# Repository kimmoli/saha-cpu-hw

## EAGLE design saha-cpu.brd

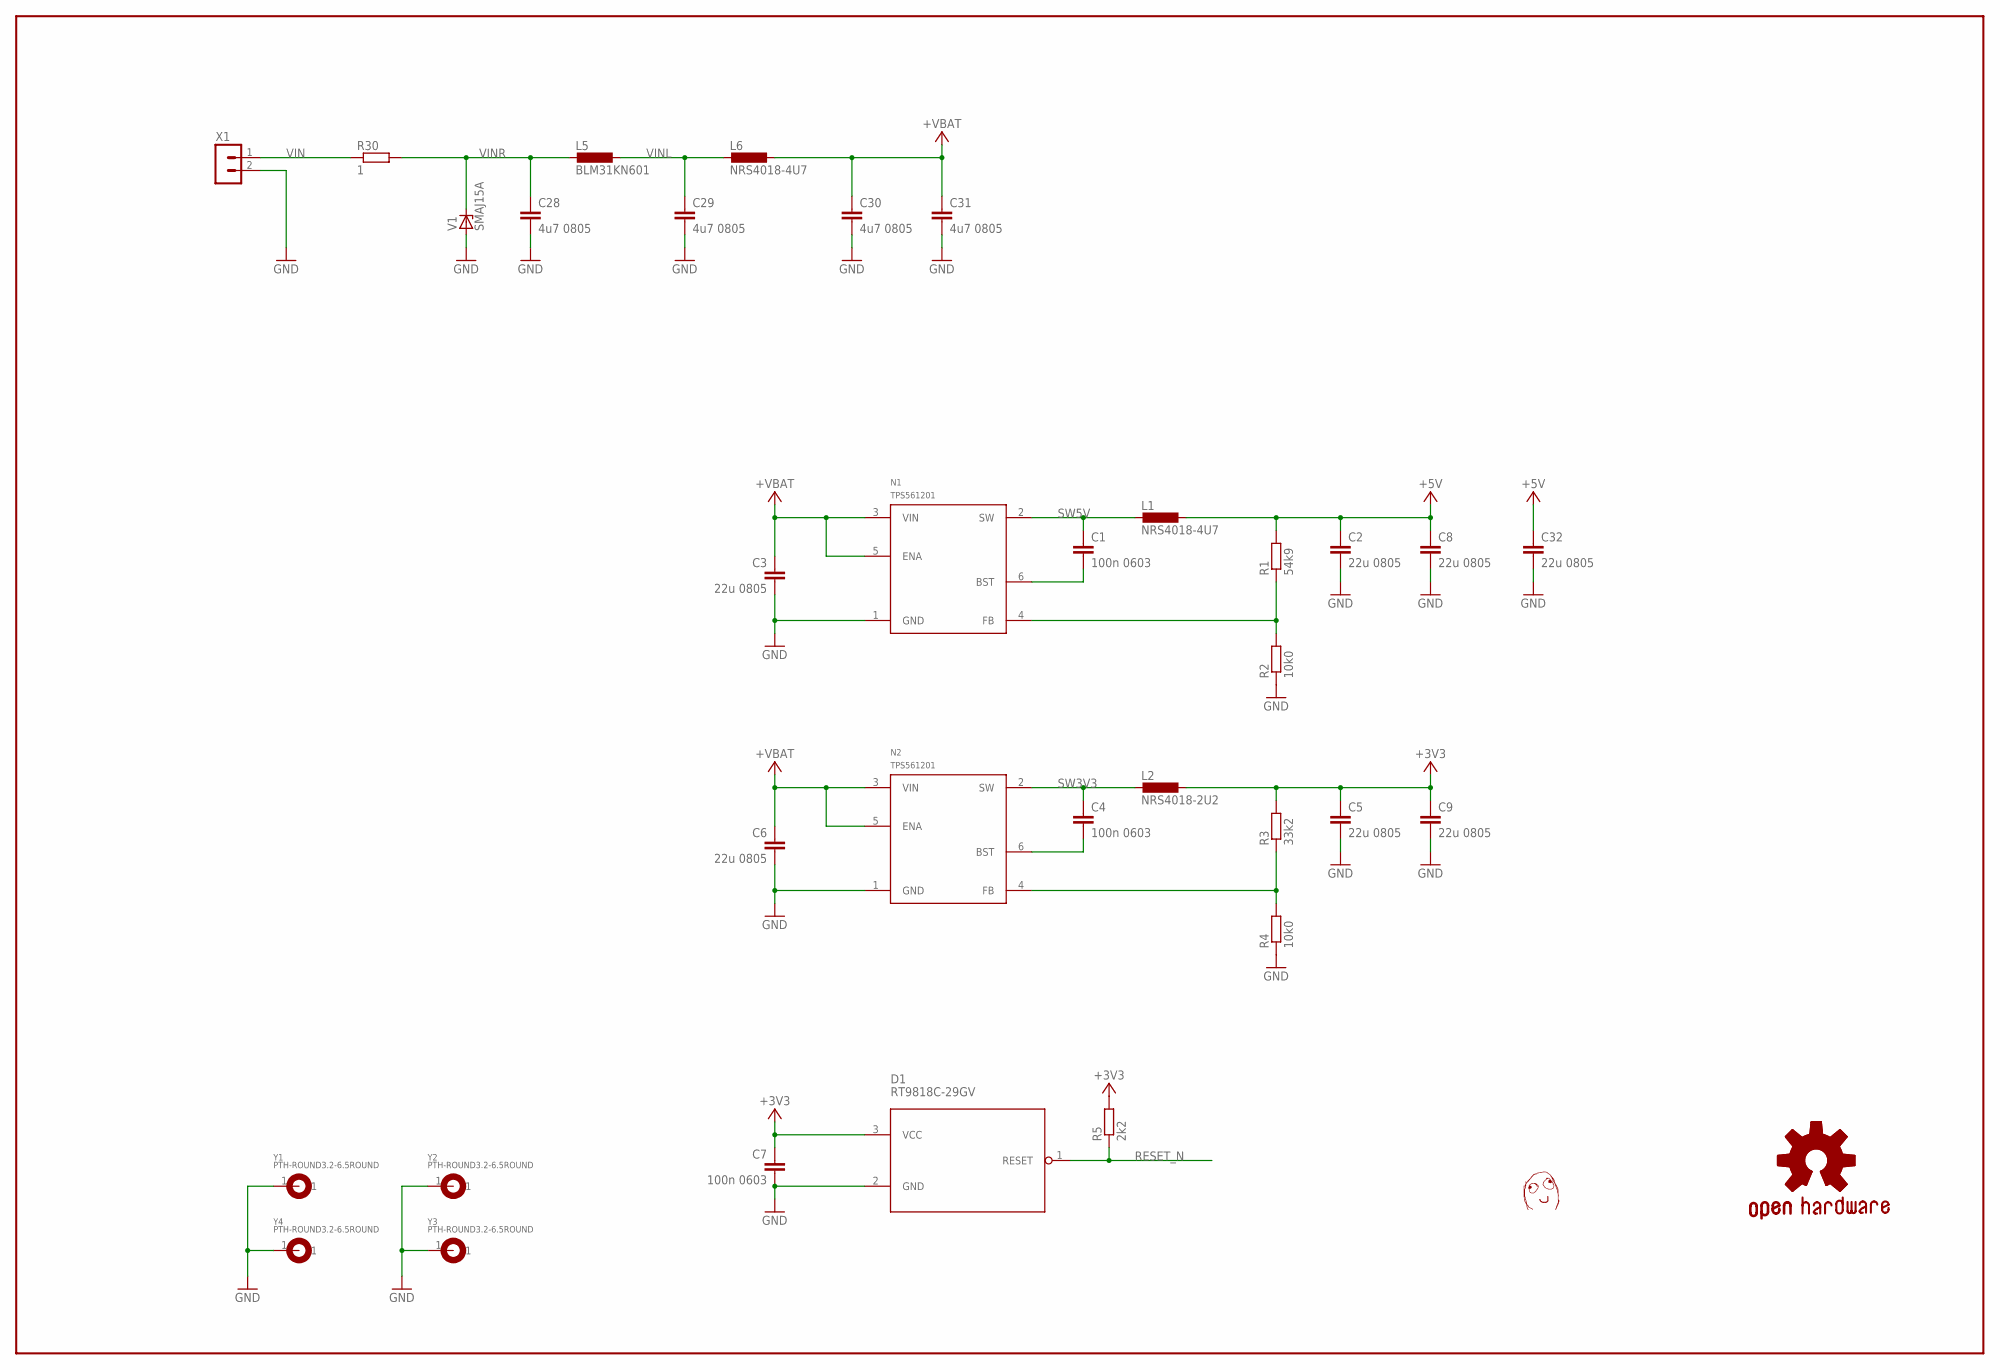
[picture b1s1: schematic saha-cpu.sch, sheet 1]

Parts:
C1, C4, C7: 100n 0603; C0603
C2, C3, C5, C6, C8, C9, C32: 22u 0805; C0805
C28, C29, C30, C31: 4u7 0805; C0805
D1: RT9818C-29GV; SOT23
L1, L6: NRS4018-4U7; NRS4018
L2: NRS4018-2U2; NRS4018
L5: BLM31KN601; R1206
N1, N2: TPS561201; OMAT_IC_2_SOT23-6
R1: 54k9; R0603
R2, R4: 10k0; R0603
R3: 33k2; R0603
R5: 2k2; R0603
R30: 1; R2512
U$1: DAFUG
V1: SMAJ15A; DO214AC
X1: TE_RUUVILIITIN2
Y1, Y2, Y3, Y4: PTH-ROUND3.2-6.5ROUND; EKE_PTH-3.2-6.5

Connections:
+3V3: C5.1, C7.1, C9.1, D1.3 (VCC), L2.1, R3.2, R5.2; also elsewhere on the board
+5V: C2.1, C8.1, C32.1, L1.1, R1.2; also elsewhere on the board
+VBAT: C3.1, C6.1, C30.1, C31.1, L6.1, N1.3 (VIN), N1.5 (ENA), N2.3 (VIN), N2.5 (ENA); also elsewhere on the board
GND: C2.2, C3.2, C5.2, C6.2, C7.2, C8.2, C9.2, C28.2, C29.2, C30.2, C31.2, C32.2, D1.2 (GND), N1.1 (GND), N2.1 (GND), R2.1, R4.1, V1.A, X1.2, Y1.1, Y2.1, Y3.1, Y4.1; also elsewhere on the board
unnamed: N2.4 (FB), R3.1, R4.2
unnamed: N1.4 (FB), R1.1, R2.2
unnamed: C1.2, N1.6 (BST)
unnamed: C4.2, N2.6 (BST)
RESET_N: D1.1 (RESET), R5.1; also elsewhere on the board
SW3V3: C4.1, L2.2, N2.2 (SW)
SW5V: C1.1, L1.2, N1.2 (SW)
VIN: R30.1, X1.1
VINL: C29.1, L5.1, L6.2
VINR: C28.1, L5.2, R30.2, V1.C

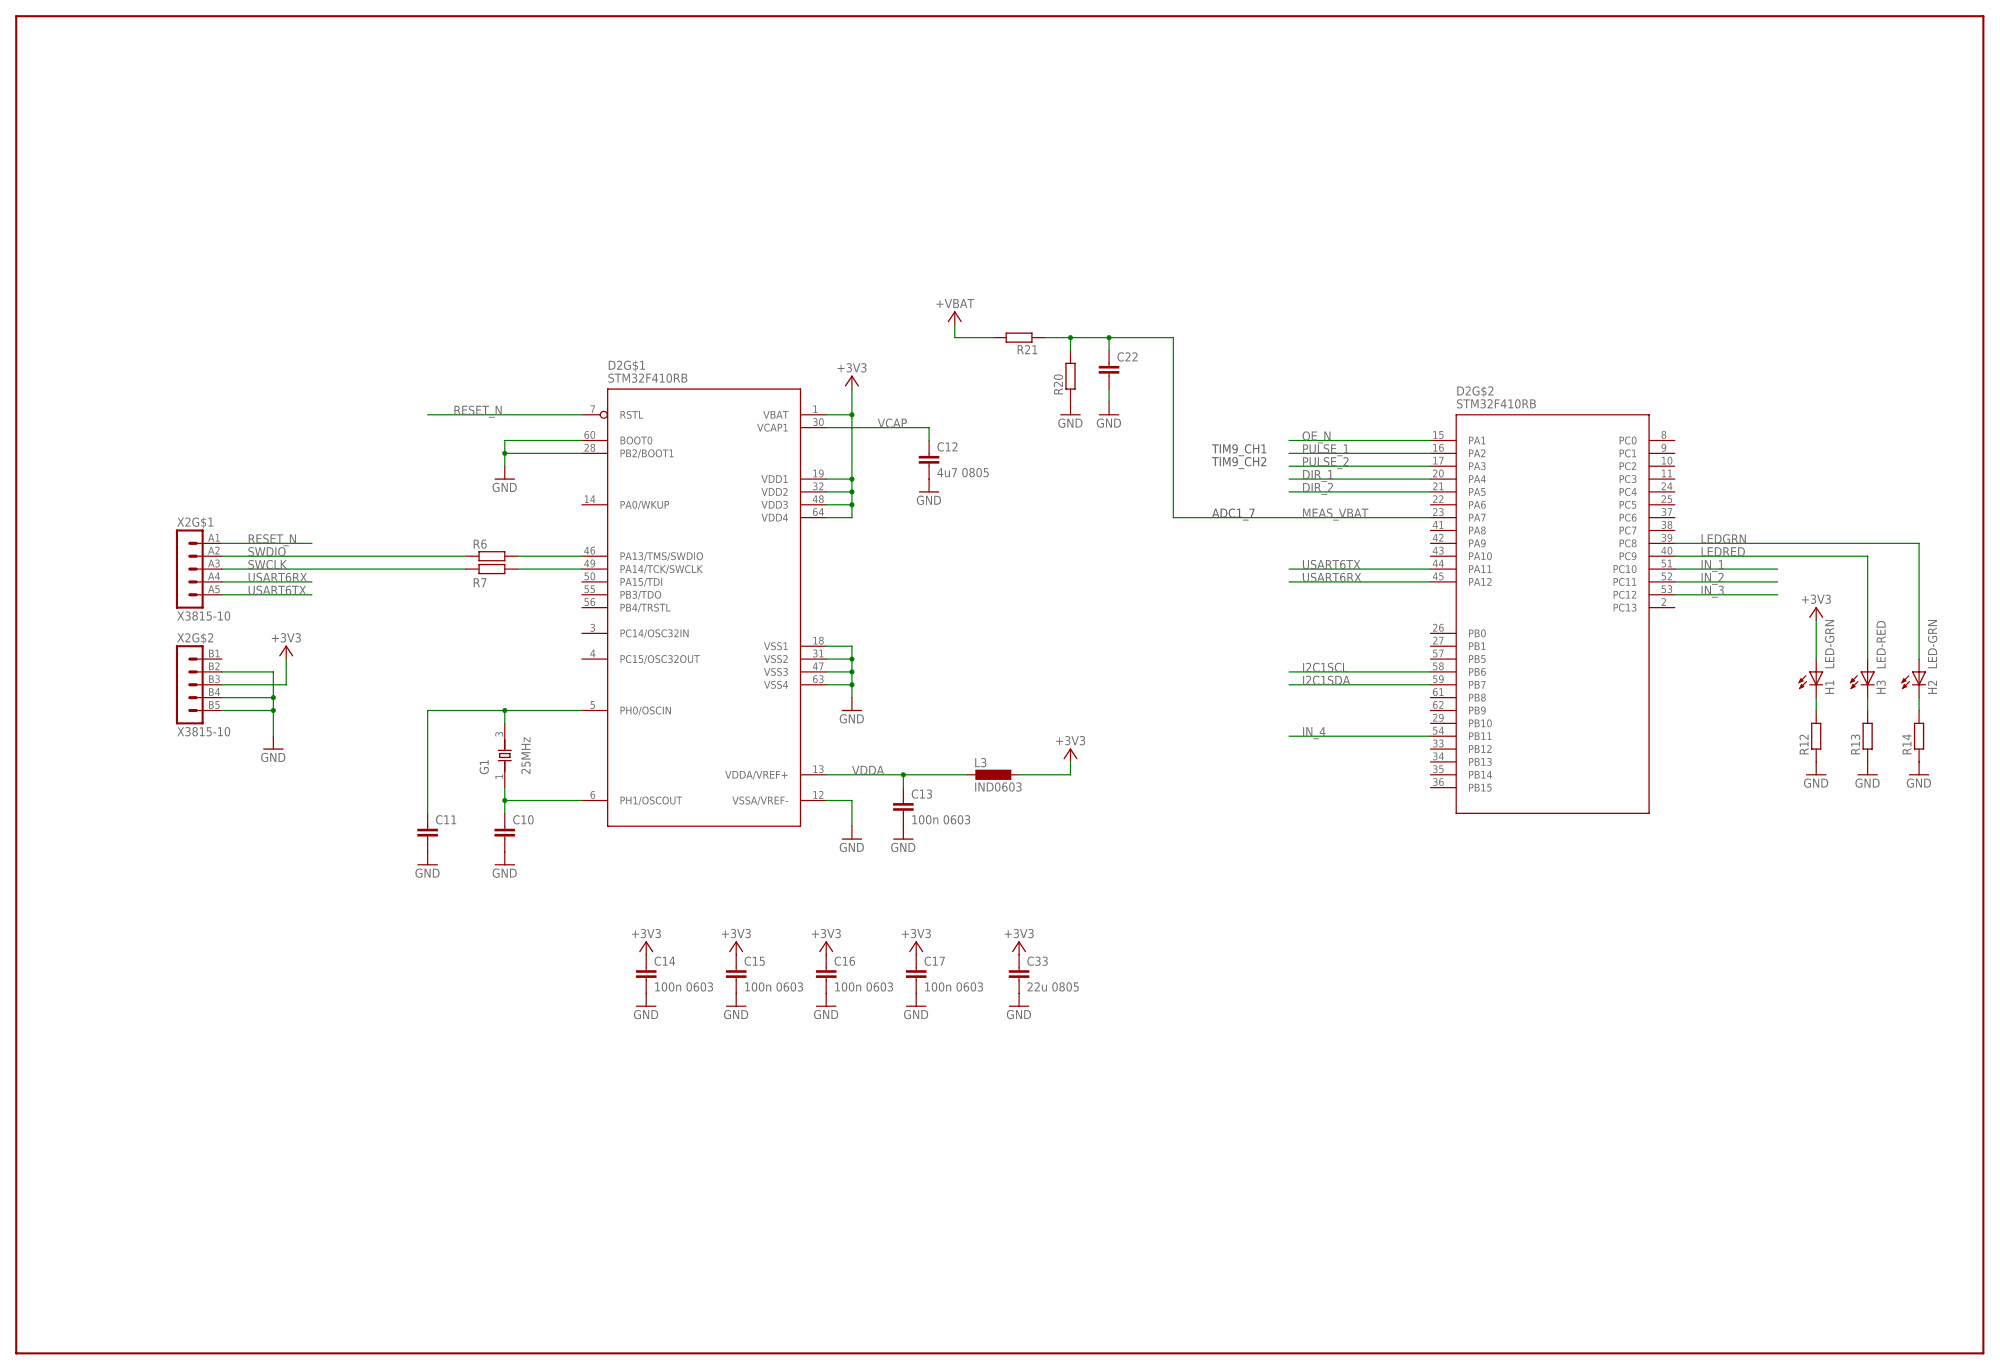
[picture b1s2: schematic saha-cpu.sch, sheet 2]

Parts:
C10, C11, C22: CAP0603; C0603
C12: 4u7 0805; C0805
C13, C14, C15, C16, C17: 100n 0603; C0603
C33: 22u 0805; C0805
D2: STM32F410RB; LQFP-64
G1: 25MHz; X_3225
H1, H2: LED-GRN; CHIP-LED0603
H3: LED-RED; CHIP-LED0603
L3: IND0603; R0603
R6, R7, R12, R13, R14, R20, R21: RES0603; R0603
X2: X3815-10; AUX-IO_LIITTIMET_15110102601

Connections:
+3V3: C14.1, C15.1, C16.1, C17.1, C33.1, D2.1 (VBAT), D2.19 (VDD1), D2.32 (VDD2), D2.48 (VDD3), D2.64 (VDD4), H1.A, L3.1, X2.B3 (3); also elsewhere on the board
+VBAT: R21.2; also elsewhere on the board
DIR_1: D2.20 (PA4); also elsewhere on the board
DIR_2: D2.21 (PA5); also elsewhere on the board
GND: C10.2, C11.2, C12.2, C13.2, C14.2, C15.2, C16.2, C17.2, C22.2, C33.2, D2.12 (VSSA/VREF-), D2.18 (VSS1), D2.28 (PB2/BOOT1), D2.31 (VSS2), D2.47 (VSS3), D2.60 (BOOT0), D2.63 (VSS4), R12.1, R13.1, R14.1, R20.1, X2.B2 (2), X2.B4 (4), X2.B5 (5); also elsewhere on the board
I2C1SCL: D2.58 (PB6); also elsewhere on the board
I2C1SDA: D2.59 (PB7); also elsewhere on the board
IN_1: D2.51 (PC10); also elsewhere on the board
IN_2: D2.52 (PC11); also elsewhere on the board
IN_3: D2.53 (PC12); also elsewhere on the board
IN_4: D2.54 (PB11); also elsewhere on the board
LEDGRN: D2.39 (PC8), H2.A
LEDRED: D2.40 (PC9), H3.A
MEAS_VBAT: C22.1, D2.23 (PA7), R20.2, R21.1
unnamed: H1.C, R12.2
unnamed: H3.C, R13.2
unnamed: H2.C, R14.2
OE_N: D2.15 (PA1); also elsewhere on the board
OSCIN: C11.1, D2.5 (PH0/OSCIN), G1.3 (X2)
OSCOUT: C10.1, D2.6 (PH1/OSCOUT), G1.1 (X1)
PULSE_1: D2.16 (PA2); also elsewhere on the board
PULSE_2: D2.17 (PA3); also elsewhere on the board
RESET_N: D2.7 (RSTL), X2.A1 (1); also elsewhere on the board
SWCLK: R7.1, X2.A3 (3)
SWCLK-CPU: D2.49 (PA14/TCK/SWCLK), R7.2
SWDIO: R6.1, X2.A2 (2)
SWDIO-CPU: D2.46 (PA13/TMS/SWDIO), R6.2
USART6RX: D2.45 (PA12), X2.A4 (4)
USART6TX: D2.44 (PA11), X2.A5 (5)
VCAP: C12.1, D2.30 (VCAP1)
VDDA: C13.1, D2.13 (VDDA/VREF+), L3.2

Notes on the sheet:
ADC1_7
TIM9_CH1
TIM9_CH2

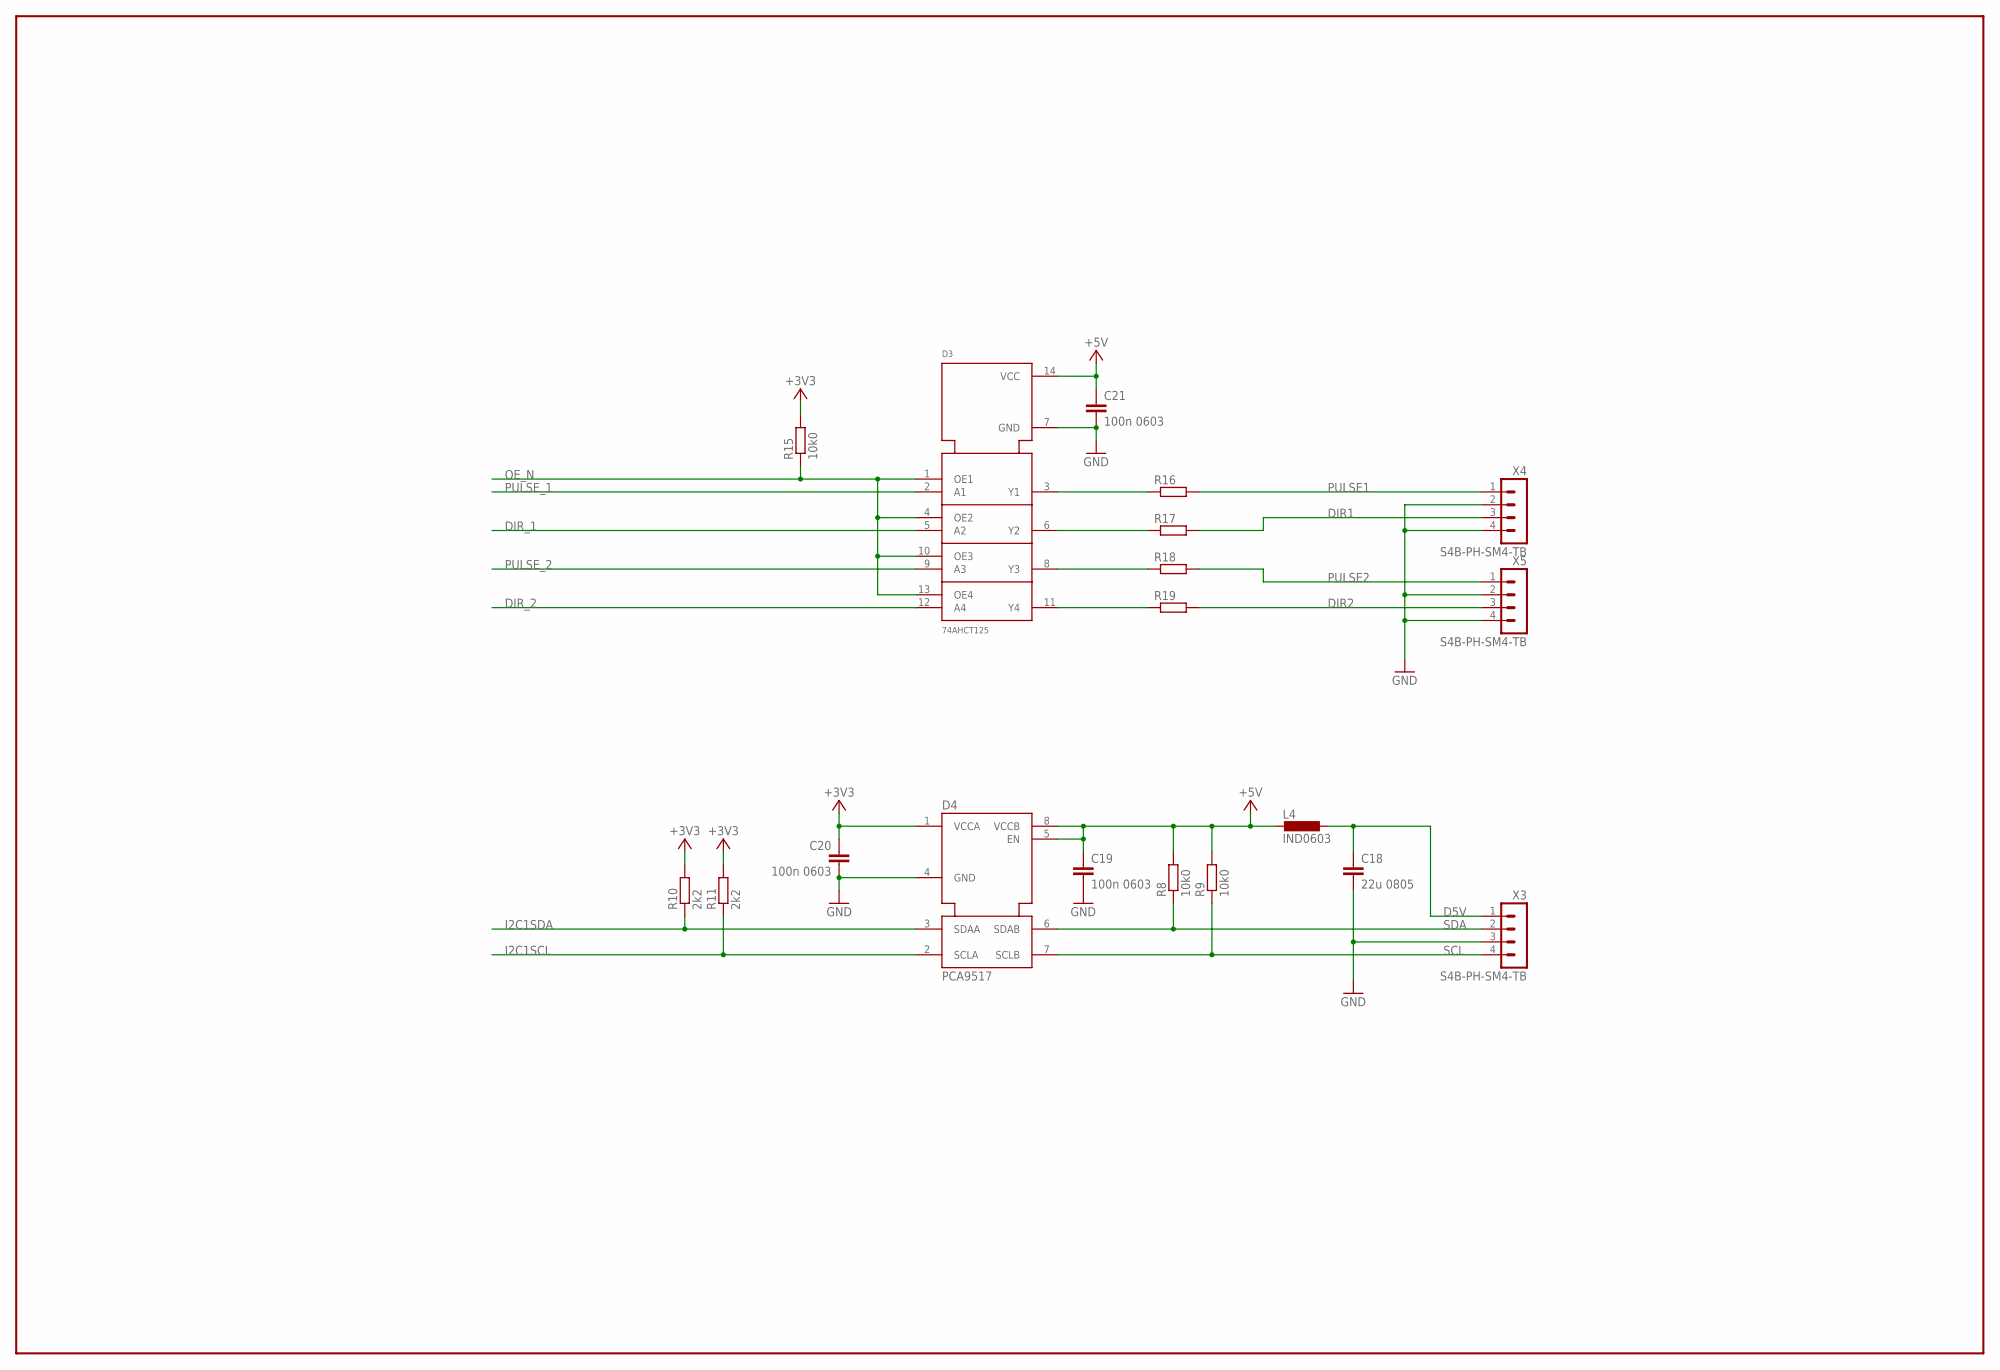
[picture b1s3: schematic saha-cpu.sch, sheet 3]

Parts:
C18: 22u 0805; C0805
C19, C20, C21: 100n 0603; C0603
D3: 74AHCT125; SO14
D4: PCA9517; OMAT_IC_2_SOIC8-N_MC
L4: IND0603; R0603
R8, R9, R15: 10k0; R0603
R10, R11: 2k2; R0603
R16, R17, R18, R19: RES0603; R0603
X3, X4, X5: S4B-PH-SM4-TB; JST-PH2.0-RA-4

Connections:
+3V3: C20.1, D4.1 (VCCA), R10.2, R11.2, R15.2; also elsewhere on the board
+5V: C19.1, C21.1, D3.14 (VCC), D4.5 (EN), D4.8 (VCCB), L4.2, R8.2, R9.2; also elsewhere on the board
D5V: C18.1, L4.1, X3.1
DIR1: R17.2, X4.3
DIR2: R19.2, X5.3
DIR_1: D3.5 (A2); also elsewhere on the board
DIR_2: D3.12 (A4); also elsewhere on the board
GND: C18.2, C19.2, C20.2, C21.2, D3.7 (GND), D4.4 (GND), X3.3, X4.2, X4.4, X5.2, X5.4; also elsewhere on the board
I2C1SCL: D4.2 (SCLA), R11.1; also elsewhere on the board
I2C1SDA: D4.3 (SDAA), R10.1; also elsewhere on the board
unnamed: D3.11 (Y4), R19.1
unnamed: D3.8 (Y3), R18.1
unnamed: D3.6 (Y2), R17.1
unnamed: D3.3 (Y1), R16.1
OE_N: D3.1 (OE1), D3.4 (OE2), D3.10 (OE3), D3.13 (OE4), R15.1; also elsewhere on the board
PULSE1: R16.2, X4.1
PULSE2: R18.2, X5.1
PULSE_1: D3.2 (A1); also elsewhere on the board
PULSE_2: D3.9 (A3); also elsewhere on the board
SCL: D4.7 (SCLB), R9.1, X3.4
SDA: D4.6 (SDAB), R8.1, X3.2

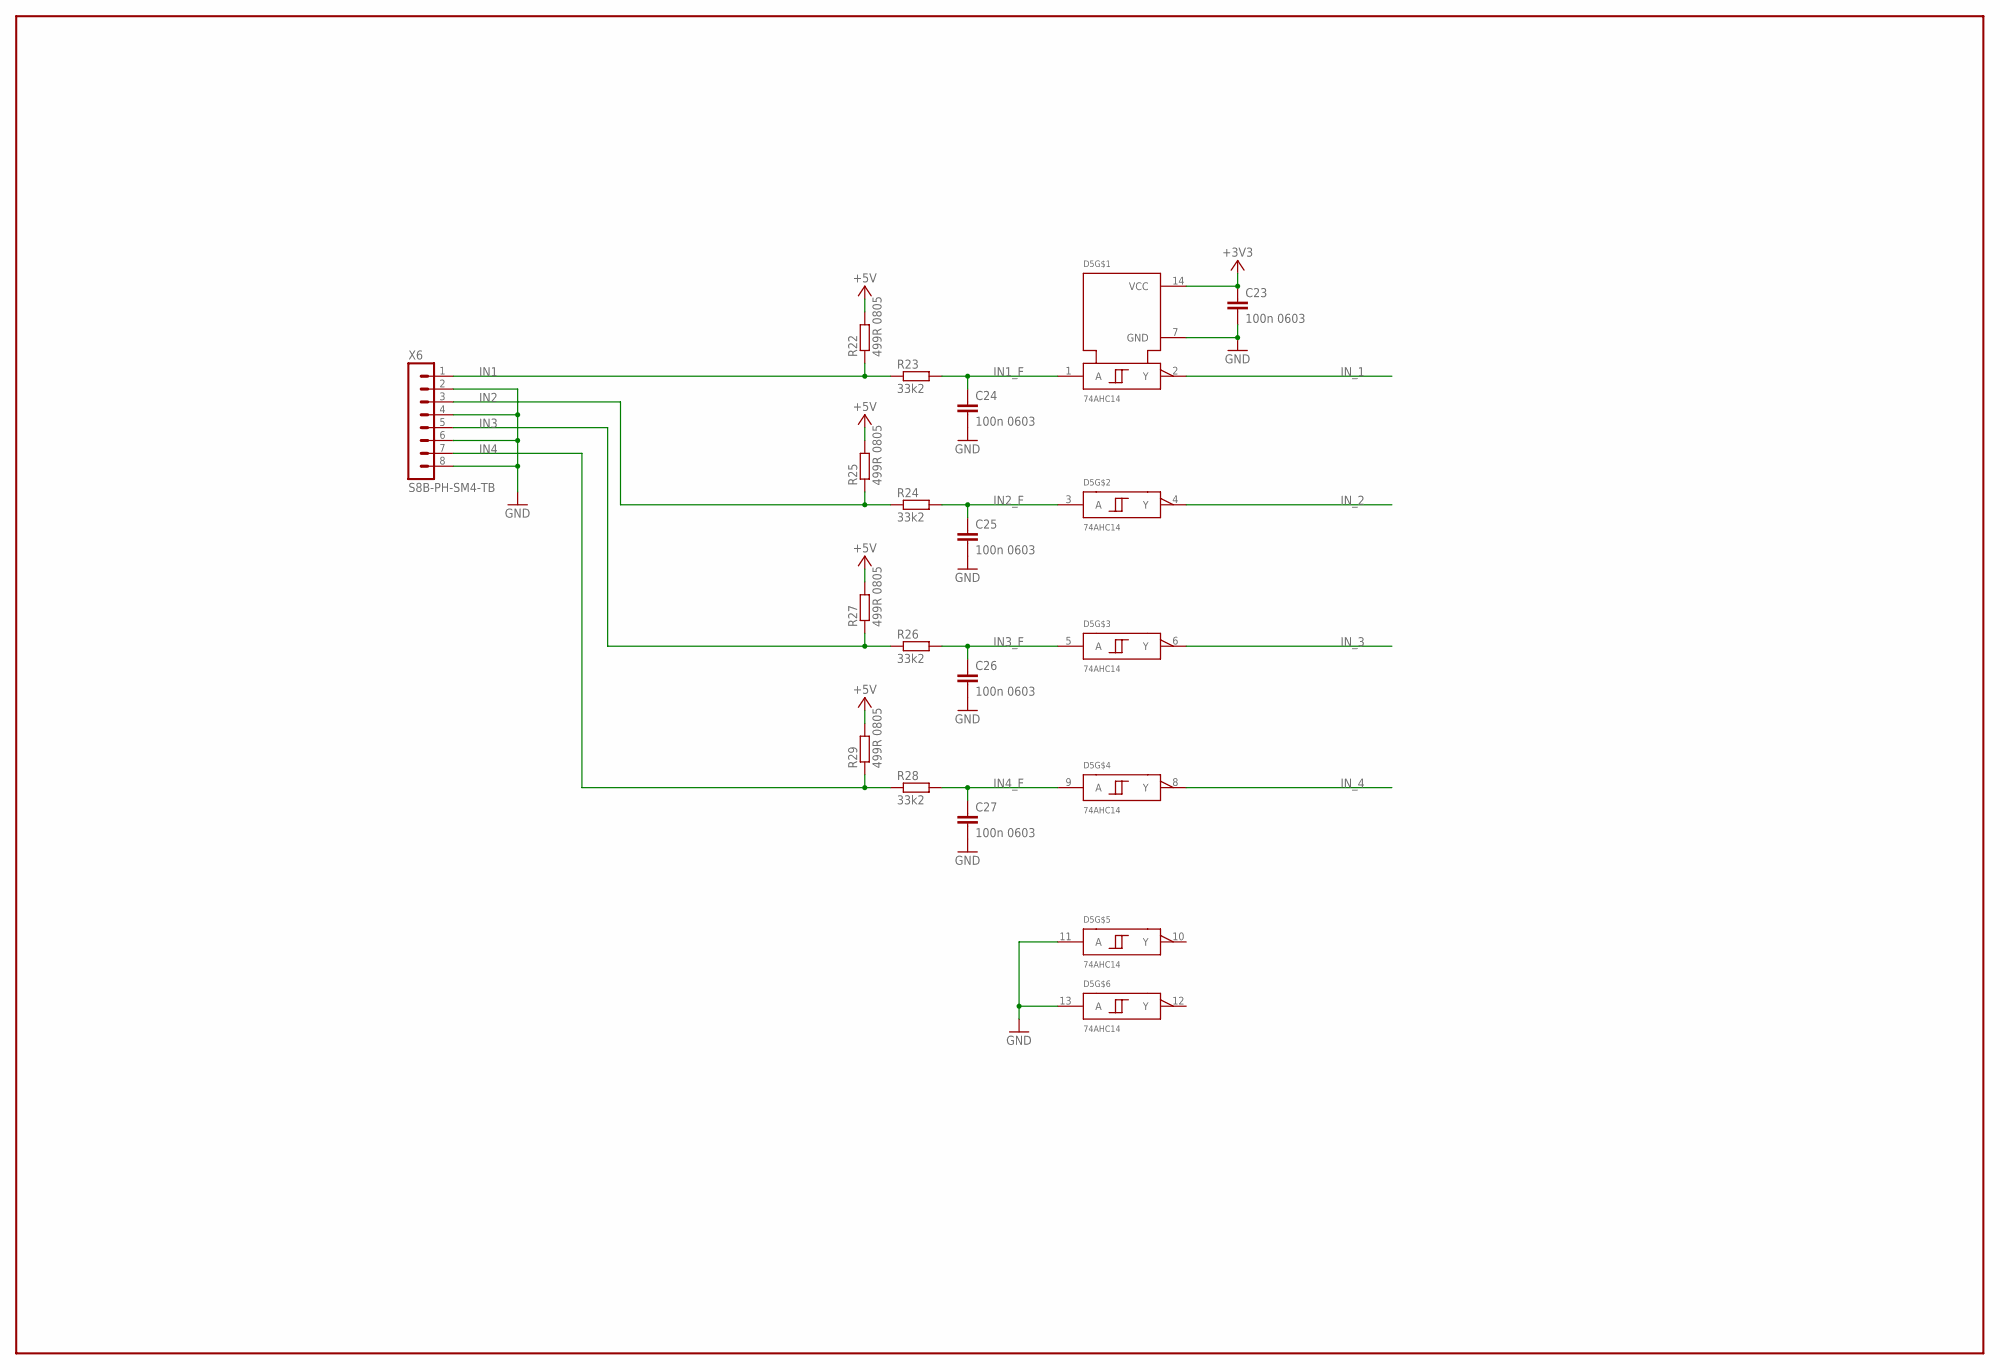
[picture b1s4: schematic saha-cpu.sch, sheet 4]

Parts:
C23, C24, C25, C26, C27: 100n 0603; C0603
D5: 74AHC14; SO14
R22, R25, R27, R29: 499R 0805; R0805
R23, R24, R26, R28: 33k2; R0603
X6: S8B-PH-SM4-TB; JST-PH2.0-RA-8

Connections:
+3V3: C23.1, D5.14 (VCC); also elsewhere on the board
+5V: R22.2, R25.2, R27.2, R29.2; also elsewhere on the board
GND: C23.2, C24.2, C25.2, C26.2, C27.2, D5.7 (GND), D5.11 (A), D5.13 (A), X6.2, X6.4, X6.6, X6.8; also elsewhere on the board
IN1: R22.1, R23.1, X6.1
IN1_F: C24.1, D5.1 (A), R23.2
IN2: R24.1, R25.1, X6.3
IN2_F: C25.1, D5.3 (A), R24.2
IN3: R26.1, R27.1, X6.5
IN3_F: C26.1, D5.5 (A), R26.2
IN4: R28.1, R29.1, X6.7
IN4_F: C27.1, D5.9 (A), R28.2
IN_1: D5.2 (Y); also elsewhere on the board
IN_2: D5.4 (Y); also elsewhere on the board
IN_3: D5.6 (Y); also elsewhere on the board
IN_4: D5.8 (Y); also elsewhere on the board

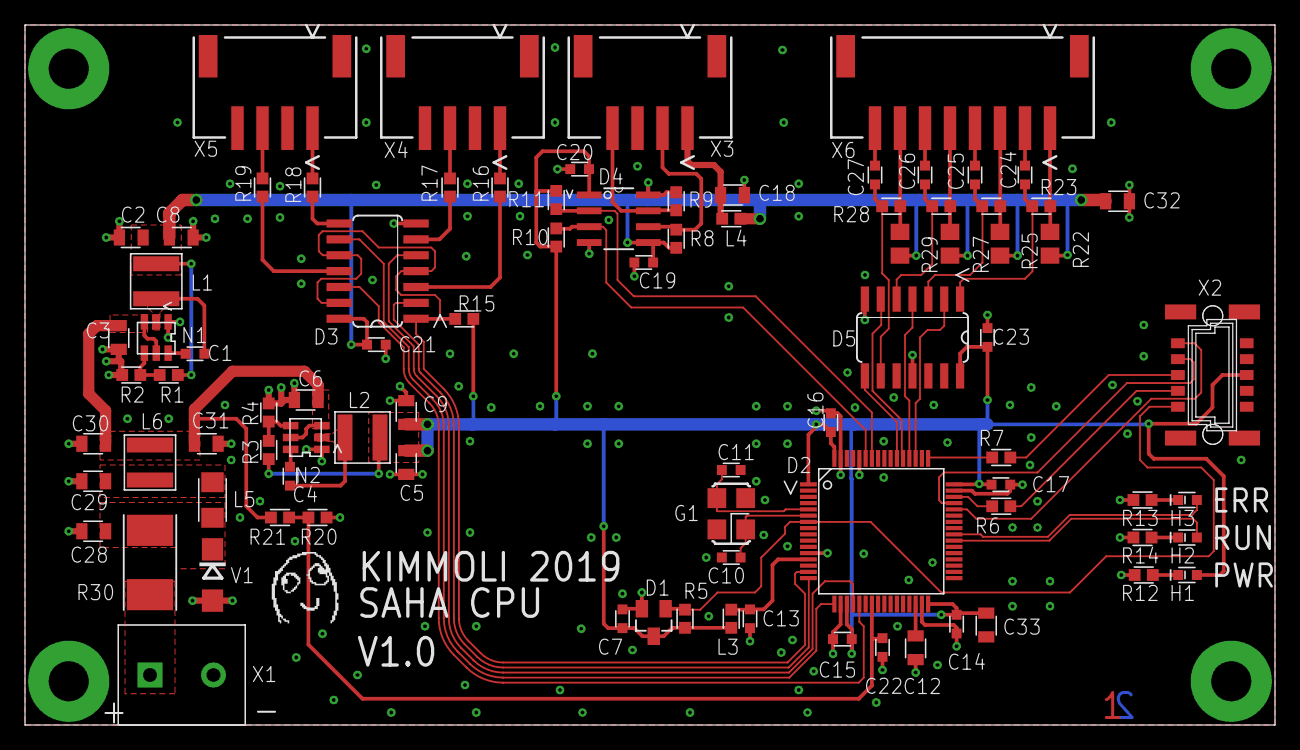
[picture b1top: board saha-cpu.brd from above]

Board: 2 copper layers, 100.0 x 56.0 mm, 92 parts (0 on the bottom side), 60 nets.

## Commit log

2019-05-04 schematic update
2019-05-04 Initial placement
2019-05-04 Initial routing complete
2019-05-04 routing finished
2019-05-04 add pdf
2019-05-04 fine tuning
